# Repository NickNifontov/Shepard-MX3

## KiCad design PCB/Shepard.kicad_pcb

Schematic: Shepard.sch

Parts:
BAT1: 1K; Potentiometer_Bourns_3296W_Vertical
C1, C10: 33uf 100V; CP_Radial_D8.0mm_P5.00mm
C2, C6, C7, C14, C15: 10uf; C_1206_3216Metric_Pad1.42x1.75mm_HandSolder
C3, C4, C5, C8, C9, C11, C21, C22, C26, C27, C28: 0.1uf; C_1206_3216Metric_Pad1.42x1.75mm_HandSolder
C12: 10 uf; CP_Radial_D5.0mm_P2.50mm
C13: 10 uf; C_Elec_5x5.4
C16: 0.1uf 100V; C_1206_3216Metric_Pad1.42x1.75mm_HandSolder
C17: 33nf; C_1206_3216Metric_Pad1.42x1.75mm_HandSolder
C18: 1uf; C_1206_3216Metric_Pad1.42x1.75mm_HandSolder
C19, C20: 100uf 25v; CP_Radial_D8.0mm_P5.00mm
C23, C30: 33uf 100v; C_Elec_10x10.2
C24, C25: 220uf 25v; C_Elec_8x10.2
D1, D2, D3, D4, D7: 1N4007; D_1206_3216Metric_Pad1.42x1.75mm_HandSolder
D5, D10: Zener 4V2; D_1206_3216Metric_Pad1.42x1.75mm_HandSolder
D6: XL7015; TO-252-5_TabPin3
D9, D12: S210; D_SMB
D11: BAS86; D_MiniMELF
D15: BLOCK; LED_1206_3216Metric_Pad1.42x1.75mm_HandSolder
D17: STAT; LED_1206_3216Metric_Pad1.42x1.75mm_HandSolder
D20: smbj20A; D_SMB
H1, H2, H3, H4: MountingHole; MountingHole_2.2mm_M2_DIN965_Pad
J1: ADC RAW G; PinHeader_1x03_P2.54mm_Horizontal
J2: RELAY; PinHeader_1x10_P2.54mm_Horizontal
J3: ON/OFF; PinHeader_1x02_P2.54mm_Horizontal
J4: 3V3 DIO CLK G; PinHeader_1x04_P2.54mm_Vertical
J5: TO_MX3; PinHeader_1x05_P2.54mm_Horizontal
J6: IN_AC; PinHeader_1x02_P2.54mm_Horizontal
J7: OUT_AC; PinHeader_1x02_P2.54mm_Horizontal
J8: RESTART; PinHeader_1x04_P2.54mm_Horizontal
K1, K2, K3, K4, K5: TIANBO-HJR-4102-L; Relay_SPDT_HJR-4102
L1: 47uf; L_Radial_D8.7mm_P5.00mm_Fastron_07HCP
L2: 47uf; L_12x12mm_H8mm
L3: bead; L_0805_2012Metric_Pad1.15x1.40mm_HandSolder
Q1, Q2, Q3, Q4, Q5, Q6, Q8: BC817; SOT-23_Handsoldering
Q9: BCX53; SOT-89-3
R1, R14: 100; R_1206_3216Metric_Pad1.42x1.75mm_HandSolder
R2, R5, R9, R47, R53, R59, R60: 5K; R_1206_3216Metric_Pad1.42x1.75mm_HandSolder
R3: 20; R_1206_3216Metric_Pad1.42x1.75mm_HandSolder
R4: R0; R_0805_2012Metric_Pad1.15x1.40mm_HandSolder
R6, R13, R15, R19, R20, R31, R33, R36, R37, R40, R41: 0; R_1206_3216Metric_Pad1.42x1.75mm_HandSolder
R7, R48, R54: 4K7; R_1206_3216Metric_Pad1.42x1.75mm_HandSolder
R8: 20K; R_1206_3216Metric_Pad1.42x1.75mm_HandSolder
R10, R12, R16, R21, R23, R26, R32, R34, R38, R57: 1K; R_1206_3216Metric_Pad1.42x1.75mm_HandSolder
R11, R17, R18, R22, R30, R35, R39, R58, R61, R66, R67: 10K; R_1206_3216Metric_Pad1.42x1.75mm_HandSolder
R24, R68: 100K; R_1206_3216Metric_Pad1.42x1.75mm_HandSolder
R25: 1K8; R_1206_3216Metric_Pad1.42x1.75mm_HandSolder
R27: 30K; R_1206_3216Metric_Pad1.42x1.75mm_HandSolder
R28: 1K6; R_1206_3216Metric_Pad1.42x1.75mm_HandSolder
R29: 1K2; R_1206_3216Metric_Pad1.42x1.75mm_HandSolder
R42, R43, R45, R46, R49, R50, R51, R52: 45K; R_1206_3216Metric_Pad1.42x1.75mm_HandSolder
R44, R71: 300-600; R_1206_3216Metric_Pad1.42x1.75mm_HandSolder
U1: LM317_3PinPackage; TO-252-2
U2: STM32L031F6Px; TSSOP-20_4.4x6.5mm_P0.65mm
U3: AMS1117-3.3; SOT-223-3_TabPin2
U4, U5, U6: PC817; DIP-4_W7.62mm

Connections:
15V1_OK: J5.1, Q9.2 (C)
+9V: C2.1, C6.2, C9.2, C21.1, D1.1 (K), D2.1 (K), D3.1 (K), D4.1 (K), D7.1 (K), K1.5, K2.5, K3.5, K4.5, K5.5, R1.2, R13.1, R19.1, R23.1, R29.1, R31.1, R36.1, R40.1, U1.2 (VO), U3.3 (VI)
+15V: C7.1, C8.2, C17.2, C18.2, C19.1, C20.1, C24.1, C25.1, L1.2, L2.2, Q9.3 (E), R3.2, R27.2, R60.1, U1.3 (VI)
+48V: C1.1, C10.1, C16.2, C23.1, C30.1, D6.1 (VIN), D9.1 (K), R4.1, R17.1
AB: BAT1.2, C3.1, D10.1 (K), U2.7 (PA1)
AB_RAW: J1.1, R4.2, R8.1
BLOCK_PORT: R21.1, U2.12 (PA6)
BLOCK_POWER: R57.2, R71.2, U2.14 (PB1)
BLOCK_PU: D11.1 (K), J5.3, R24.1
CLK: J4.2, R66.2, U2.20 (PA14)
COIL_2_OUT: C1.2, C2.2, C3.2, C4.1, C5.2, C6.1, C7.2, C8.1, C9.1, C10.2, C11.2, C12.2, C13.2, C14.2, C15.1, C16.1, C18.1, C19.2, C20.2, C21.2, C22.2, C23.2, C24.2, C25.2, C26.2, C27.2, C28.2, C30.2, D5.2 (A), D6.3 (GND), D10.2 (A), D12.2 (A), D15.1 (K), D17.1 (K), D20.2 (A), J1.3, J3.1, J4.1, J5.2, J8.3, Q1.2 (E), Q2.2 (E), Q3.2 (E), Q4.2 (E), Q5.2 (E), Q6.2 (E), Q8.2 (E), R6.1, R12.1, R14.2, R24.2, R25.2, R32.1, R58.1, R66.1, R68.1, U2.15 (VSS), U3.1 (GND), U4.3, U5.3, U6.3
DIO: J4.3, R61.1, U2.19 (PA13)
IN_1A: J2.1, K1.7, R15.1
IN_1B: J2.2, K1.6
IN_2A: J2.3, K2.7, R20.1
IN_2B: J2.4, K2.6
IN_3A: J2.5, K3.7, R33.1
IN_3B: J2.6, K3.6
IN_4A: J2.7, K4.7, R37.1
IN_4B: J2.8, K4.6
IN_5A: J2.9, K5.7, R41.1
IN_5B: J2.10, K5.6
IN_AC: C27.1, R48.1, U2.6 (PA0), U5.4
IN_L: J6.1, R42.2
IN_N: J6.2, R43.2
LED: R44.2, U2.17 (PA9)
NRST: C26.1, R67.1, U2.4 (NRST)
unnamed: BAT1.1, R8.2
unnamed: BAT1.3, R14.1
unnamed: C11.1, C15.2, L3.1, U2.5 (VDDA)
unnamed: D1.2 (A), K1.8, Q1.3 (C)
unnamed: D2.2 (A), K2.8, Q3.3 (C)
unnamed: D3.2 (A), K3.8, Q4.3 (C)
unnamed: D4.2 (A), K4.8, Q5.3 (C)
unnamed: D7.2 (A), K5.8, Q6.3 (C)
unnamed: D11.2 (A), Q2.3 (C), R23.2
unnamed: D6.2 (SW), D12.1 (K), L1.1, L2.1
unnamed: D15.2 (A), R71.1
unnamed: D17.2 (A), R44.1
unnamed: D9.2 (A), D20.1 (K), J1.2
unnamed: J5.5, R3.1
unnamed: J8.2, R1.1
unnamed: K1.1, K1.12, R13.2, R15.2
unnamed: K2.1, K2.12, R19.2, R20.2
unnamed: K3.1, K3.12, R31.2, R33.2
unnamed: K4.1, K4.12, R36.2, R37.2
unnamed: K5.1, K5.12, R40.2, R41.2
unnamed: Q1.1 (B), R10.1, R11.2
unnamed: Q2.1 (B), R21.2, R22.2
unnamed: Q3.1 (B), R16.1, R18.2
unnamed: Q4.1 (B), R26.1, R30.2
unnamed: Q5.1 (B), R34.1, R35.2
unnamed: Q6.1 (B), R38.1, R39.2
unnamed: Q8.1 (B), R57.1, R58.2
unnamed: Q8.3 (C), R59.2
unnamed: Q9.1 (B), R59.1, R60.2
unnamed: R2.1, R5.2, U4.1
unnamed: R25.1, R29.2, U1.1 (ADJ)
unnamed: R28.1, R32.2
unnamed: R42.1, R45.2
unnamed: R43.1, R46.2
unnamed: R45.1, R47.2, U5.1
unnamed: R46.1, R47.1, U5.2
unnamed: R49.1, R51.2
unnamed: R50.1, R52.2
unnamed: R51.1, R53.2, U6.1
unnamed: R52.1, R53.1, U6.2
unnamed: R68.2, U2.1 (BOOT0)
OUT_AC: C28.1, R54.1, U2.9 (PA3), U6.4
OUT_L: J7.1, R49.2
OUT_N: J7.2, R50.2
RELAY_1: R10.2, U2.18 (PA10)
RELAY_2: R16.2, U2.3 (PC15)
RELAY_3: R26.2, U2.13 (PA7)
RELAY_4: R34.2, U2.11 (PA5)
RELAY_5: R38.2, U2.10 (PA4)
RESTART: J8.1, R2.2
RESTART_CMD: R7.1, U2.2 (PC14), U4.4
RESTART_GND: J8.4, R5.1, R6.2, U4.2
TEMP_2: J5.4, R9.2
TEMP_ADC: C5.1, D5.1 (K), R9.1, R12.2, U2.8 (PA2)
XL_EN: D6.5 (EN), J3.2, R17.2
XL_FB: C17.1, D6.4 (FB), R27.1, R28.2

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
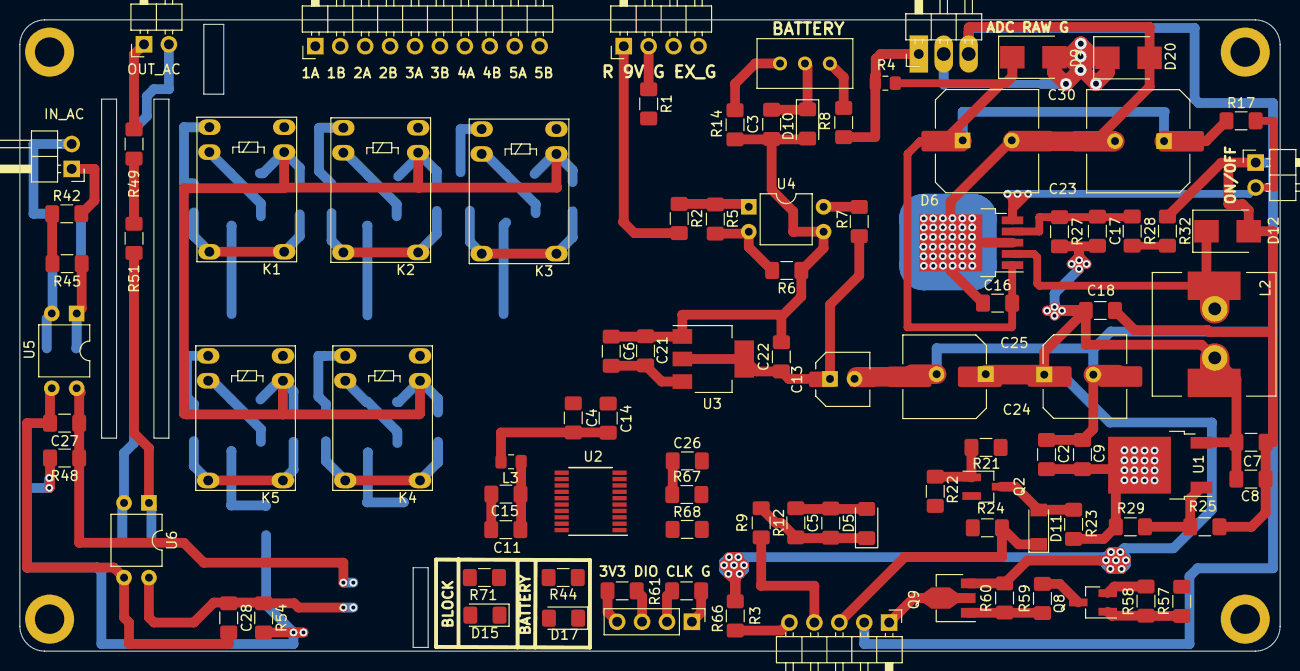
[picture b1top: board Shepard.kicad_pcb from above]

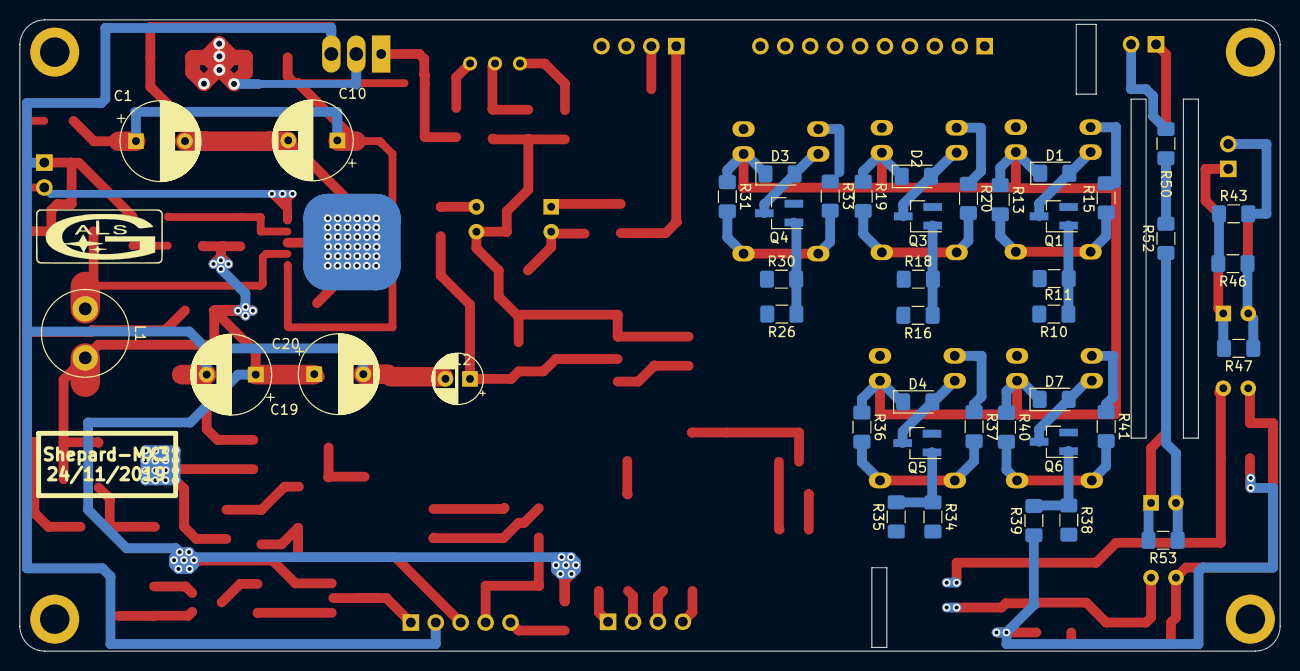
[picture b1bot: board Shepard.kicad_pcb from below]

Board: 2 copper layers, 128.4 x 64.3 mm, 141 parts (42 on the bottom side), 84 nets.

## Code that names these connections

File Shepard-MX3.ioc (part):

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Mcu.Name=STM32L031F(4-6)Px
Mcu.Package=TSSOP20
Mcu.UserName=STM32L031F6Px
PA0-CK_IN.GPIOParameters=GPIO_Label
PA0-CK_IN.GPIO_Label=IN_AC
PA0-CK_IN.Mode=IN0
PA0-CK_IN.Signal=ADC_IN0
PA1.GPIOParameters=GPIO_Label
PA1.GPIO_Label=AB
PA1.Mode=IN1
PA1.Signal=ADC_IN1
PA10.GPIOParameters=GPIO_Speed,PinState,GPIO_Label
PA10.GPIO_Label=RELAY_1
PA10.GPIO_Speed=GPIO_SPEED_FREQ_VERY_HIGH
PA10.PinState=GPIO_PIN_SET
PA10.Signal=GPIO_Output
PA13.GPIOParameters=GPIO_Label
PA13.GPIO_Label=DIO
PA13.Mode=Serial_Wire
PA13.Signal=SYS_SWDIO
PA14.GPIOParameters=GPIO_Label
PA14.GPIO_Label=CLK
PA14.Mode=Serial_Wire
PA14.Signal=SYS_SWCLK
PA2.GPIOParameters=GPIO_Label
PA2.GPIO_Label=TEMP_ADC
PA2.Mode=IN2
PA2.Signal=ADC_IN2
PA3.GPIOParameters=GPIO_Label
PA3.GPIO_Label=OUT_AC
PA3.Mode=IN3
PA3.Signal=ADC_IN3
PA4.GPIOParameters=GPIO_Speed,PinState,GPIO_Label
PA4.GPIO_Label=RELAY_5
PA4.GPIO_Speed=GPIO_SPEED_FREQ_VERY_HIGH
PA4.PinState=GPIO_PIN_SET
PA4.Signal=GPIO_Output
PA5.GPIOParameters=GPIO_Speed,PinState,GPIO_Label
PA5.GPIO_Label=RELAY_4
PA5.GPIO_Speed=GPIO_SPEED_FREQ_VERY_HIGH
PA5.PinState=GPIO_PIN_SET
PA5.Signal=GPIO_Output
PA6.GPIOParameters=GPIO_Speed,PinState,GPIO_Label
PA6.GPIO_Label=BLOCK_PORT
PA6.GPIO_Speed=GPIO_SPEED_FREQ_VERY_HIGH
PA6.PinState=GPIO_PIN_SET
PA6.Signal=GPIO_Output
PA7.GPIOParameters=GPIO_Speed,PinState,GPIO_Label
PA7.GPIO_Label=RELAY_3
PA7.GPIO_Speed=GPIO_SPEED_FREQ_VERY_HIGH
PA7.PinState=GPIO_PIN_SET
PA7.Signal=GPIO_Output
PA9.GPIOParameters=GPIO_Speed,GPIO_Label
PA9.GPIO_Label=LED
PA9.GPIO_Speed=GPIO_SPEED_FREQ_VERY_HIGH
PA9.Signal=GPIO_Output
PB1.GPIOParameters=GPIO_Speed,GPIO_Label
PB1.GPIO_Label=BLOCK_POWER
PB1.GPIO_Speed=GPIO_SPEED_FREQ_VERY_HIGH
PB1.Signal=GPIO_Output
PC14-OSC32_IN.GPIOParameters=GPIO_Label,GPIO_ModeDefaultEXTI
PC14-OSC32_IN.GPIO_Label=RESTART_CMD
PC14-OSC32_IN.GPIO_ModeDefaultEXTI=GPIO_MODE_IT_RISING_FALLING
PC14-OSC32_IN.Signal=GPXTI14
PC15-OSC32_OUT.GPIOParameters=GPIO_Speed,PinState,GPIO_Label
PC15-OSC32_OUT.GPIO_Label=RELAY_2
PC15-OSC32_OUT.GPIO_Speed=GPIO_SPEED_FREQ_VERY_HIGH
PC15-OSC32_OUT.PinState=GPIO_PIN_SET
PC15-OSC32_OUT.Signal=GPIO_Output
RCC.HSE_VALUE=8000000
RCC.SYSCLKFreq_VALUE=32000000
RCC.SYSCLKSource=RCC_SYSCLKSOURCE_PLLCLK
board=custom

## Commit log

2019-12-08 first release
2019-12-08 added PCB
2020-01-03 fixed
2020-01-08 fixed bugs
2020-01-08 added gisteresi for LOW and very low AB signal
2020-01-19 release
